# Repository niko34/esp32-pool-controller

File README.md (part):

<h1> ESP32 Pool Controller</h1>

Disclaimer : projet en cours de construction.

Contrôleur automatique de piscine basé sur ESP32 :
- mesure : température, pH, ORP
- pilotage : pompe de filtration, éclairage
- correction avec pompes doseuses : pH et ORP
- interfaces : application web locale, MQTT, API

## 🎯 Fonctionnalités

### Mesures et Contrôle
- **pH** : Mesure via module numérique Atlas Scientific **EZO pH** (I²C). La température de l'eau est transmise au module pour la compensation de température de la mesure.
- **ORP (Redox)** : Mesure via module numérique Atlas Scientific **EZO ORP** (I²C)
- **Température** : Deux sondes Dallas **DS18B20** (eau + circuit/boîtier), identification automatique des rôles sur le bus OneWire
- **Historique** : Historique des mesures
- **Mode d'installation** : Décrit le câblage réel du contrôleur et garantit qu'aucun produit n'est injecté sans circulation d'eau — *PoolController pilote la filtration* (sortie 12 V), *Alimenté par le circuit de filtration*, ou *Filtration externe signalée* (une domotique tierce signale l'état via HTTP/MQTT ; dosage suspendu sans signal récent)
- **Filtration** : Programmation automatique en fonction de la température de l'eau, programmation horaire, manuel
- **Eclairage** : Programmation horaire, manuel
- **Régulation automatique de pH et ORP** : Injection de produit de correction (pH-, chlore liquide) par **régulation proportionnelle temporisée (P)** avec pause de mélange et contrôle de débit PWM. Les mesures sont **lissées** (médiane + EMA) avant d'alimenter la régulation. *(pH+ : option de configuration présente mais non gérée actuellement.)*
- **Consommation de produits** : Estimation de la consommation de produit
- **Application Web locale** : Configuration et visualisation temps réel. Accessible sur le réseau Wifi configuré (`http://poolcontroller.local`) ou un réseau Wifi de en mode point d'accès (`http://192.168.4.1`). Aucune dépendance au Cloud. [Voir les screenshots](screenshots/)
- **API** : Toutes les fonctionnalités sont exposées avec une API
- **MQTT** : Exposition des données sur MQTT. Auto-discovery HomeAssistant.
- **Mise à jour OTA** : Mise à jour firmware via interface web

### Sécurité
- ⚠️ **Limites journalières** : Protection contre le surdosage
- ⚠️ **Limites horaires** : Temps maximum d'injection par heure configurable
- ⚠️ **Watchdog** : Redémarrage automatique en cas de blocage du système (30s)
- ⚠️ **Alertes MQTT** : Notifications en cas d'anomalie

## 📋 Matériel Requis

### Module ESP32 — ⚠️ PSRAM requise

Utiliser un **ESP32-DevKitC-VE** (module **WROVER-E**, ESP32 classique **avec 8 Mo de PSRAM**) — cf. `kicad/esp32-pool-controller/BOM.xlsx`, repère U2.

> ⚠️ **Pourquoi la PSRAM est nécessaire** : la **mise à jour en ligne depuis GitHub**
> (onglet Système → « Vérifier les mises à jour ») ouvre une session TLS qui réclame
> plusieurs blocs de mémoire contigus d'environ 16 Ko. Sur un module **sans PSRAM**
> (WROOM-32), la RAM interne ne les fournit plus de façon fiable une fois le système
> démarré : la vérification échoue de manière intermittente (`BIGNUM - Memory
> allocation failed`). Avec la PSRAM, ces allocations y sont placées automatiquement
> (seuil 4 Ko) et la fonction redevient fiable.
>
> Le firmware **fonctionne** sur un WROOM-32 sans PSRAM (binaire unique, détection
> automatique au démarrage, dégradation gracieuse — depuis la v2.18.0) : régulation,
> interface web, MQTT et **mise à jour manuelle par upload de fichier** restent
> pleinement opérationnels. Seule la vérification/installation automatique depuis
> GitHub est concernée.
>
> Modules déconseillés : l'**ESP32-S3** n'est pas supporté (architecture différente,
> brochage incompatible avec le PCB v2 — les GPIO 22 et 25 utilisés par l'I²C et la
> pompe pH n'y existent pas).

### PCB

Les **sources** KiCad sont versionnées dans [`kicad/`](kicad/) :

- [Schéma électronique](screenshots/Schema.png)
- [PCB](screenshots/PCB.png)
- `kicad/esp32-pool-controller/esp32-pool-controller.kicad_sch` — schéma
- `kicad/esp32-pool-controller/esp32-pool-controller.kicad_pcb` — routage
- `kicad/esp32-pool-controller/BOM.xlsx` — nomenclature (source ; le `BOM.csv`
  s'en déduit avec `python3 tools/bom_export.py`)

Les **fichiers de fabrication** (gerbers, perçage) ne sont pas versionnés : ils se
régénèrent avec `./scripts/build-gerbers.sh` et sont publiés comme assets des
releases `pcb-vX`. Voir « Fichiers générés et releases » dans `CLAUDE.md`.

### Boîtier

Les sources FreeCAD et les STL d'impression 3D sont conservés **hors du dépôt**.

## 🧭 Reprendre le projet

Cette section s'adresse à quiconque récupère le dépôt — y compris son auteur dans
deux ans. Elle dit **où est quoi** et **comment on travaille ici**.

### Outils nécessaires

| Outil | Pour quoi | Indispensable ? |
|---|---|---|
| **PlatformIO** | compiler, téléverser, lancer les tests | oui |
| **Node.js** | `minify.js`, appelé par `build_fs.sh` | oui |
| **Chrome / Chromium** | générer les PDF de documentation | pour les releases |
| **`gh`** (GitHub CLI) | publier les releases | pour les releases |
| **KiCad 7+** | ouvrir le PCB, générer les gerbers | pour le matériel |
| **Python 3** | `tools/*.py` (BOM, coredump, couverture) | ponctuel |

⚠️ Sur macOS, `kicad-cli` et Chrome ne sont pas dans le `PATH` : les scripts
`scripts/*.sh` sondent aussi les emplacements `.app`.

### Repartir d'un clone (conteneur, autre machine)

```bash
# Debian / Ubuntu
sudo apt install -y python3 python3-pip nodejs npm chromium imagemagick zip gh
pip install --user platformio
# facultatif, seulement pour le PCB :
sudo apt install -y kicad

git clone https://github.com/niko34/esp32-pool-controller.git
cd esp32-pool-controller
pio pkg install -e esp32dev_core3   # télécharge la plateforme et les libs
pio test -e native                  # doit être vert
pio run                             # doit compiler
```

**Ce qui fonctionne depuis un clone nu** : les agents, les skills et les
commandes, les specs, les tests natifs, la compilation, la génération des PDF et
celle des gerbers. **Trois workflows GitHub Actions rejouent les trois premiers à
chaque push et à chaque PR** — tests natifs + couverture, compilation
`pio run -e esp32dev_core3`, et hygiène des specs (`./tools/check_specs.sh`,
lançable en local) : ce n'est pas une promesse, c'est une preuve. Voir
[docs/BUILD.md](docs/BUILD.md#intégration-continue-github-actions). Les scripts détectent leurs outils et échouent avec un message explicite
si l'un manque.

**Ce qui ne fonctionne pas à distance** : le déploiement sur l'appareil. Son mot
de passe n'est pas dans le dépôt — délibérément — et il vit sur un réseau local.
Il faut être sur le même réseau, et fournir le mot de passe :

```bash
./ota_update.sh firmware <adresse-ip> <mot-de-passe>
```

**Confort dégradé** : `.claude/settings.local.json` n'est pas versionné (il
contient des chemins absolus propres à une machine). Le `settings.json` partagé
couvre l'essentiel — y compris les garde-fous `deny` et `ask` — mais vous
confirmerez plus de commandes qu'en local. C'est le prix d'une configuration
qui ne présume rien de la machine.

### Où est quoi

```
src/            firmware C++ (ESP32, Arduino)      data/     interface web (vanilla JS)
test/           tests natifs — logique pure         docs/     doc technique, ADR, guides
specs/          LA SOURCE DE VÉRITÉ des demandes    kicad/    sources du PCB
scripts/        livrables de release (PDF, gerbers) tools/    utilitaires de développement
.claude/        agents, skills et commandes         builds/   archive LOCALE des binaires
```

### Comment on travaille

Le cycle est décrit en détail dans **[CLAUDE.md](CLAUDE.md)**. En résumé :

1. **Une demande = une spec** dans `specs/features/todo/`, au format du template.
   Elle se déplace vers `doing/` quand le travail commence, `done/` quand il finit,
   enrichie des notes techniques et des décisions prises.
2. **Le travail passe par des agents spécialisés** (`.claude/agents/`) :
   conception, implémentation firmware ou web, tests, revue, documentation.
   ⚠️ **`pool-chemistry` est obligatoire** dès qu'on touche au dosage, à la
   régulation ou à la calibration des sondes — ce sont les pompes qui injectent de
   l'acide et du chlore dans un bassin.
3. **Les tests natifs sont non négociables** : `pio test -e native` doit rester
   vert, et tout test neuf est **validé par mutation** — on casse volontairement le
   code qu'il protège pour vérifier qu'il meurt. Plusieurs défauts réels de ce
   projet n'ont été trouvés que comme ça.
4. **Toute décision structurante devient un ADR** dans `docs/adr/`. Les ADR sont
   immuables : on les amende d'une bannière, on ne réécrit pas leur histoire.

### Les commandes utiles

```bash
pio run                    # compiler (env unique esp32dev_core3)
pio test -e native         # 33 suites, ~1 286 cas
./build_fs.sh              # construire le filesystem web
./deploy.sh all            # flasher par USB (firmware + filesystem)
./deploy.sh ota-firmware   # mettre à jour par WiFi
./tools/coverage.sh        # couverture des tests
/release                   # publier une version firmware + doc
/release-pcb               # publier des fichiers de fabrication PCB
```

Il n'y a **qu'un seul environnement matériel**, `esp32dev_core3`. L'ancien repli
core Arduino 2.x a été retiré en v2.42.1 : il n'était plus compilable, plus
flashable, et aucun binaire de secours n'avait jamais été archivé
([ADR-0069](docs/adr/0069-retrait-repli-core-2.md)).

### Ce qui n'est pas dans le dépôt, et pourquoi

Les **fichiers générés** n'y sont pas : PDF de documentation, gerbers de
fabrication, firmware compilé. Ils sont attachés aux **releases GitHub**, où ils
sont horodatés et associés à un tag. Voir « Fichiers générés et releases » dans
[CLAUDE.md](CLAUDE.md).

**Deux exceptions volontaires**, parce que ces fichiers ne sont pas *générés* mais
*relevés* — rien ne les régénère :

- **`docs/incidents/`** — les coredumps de production et leurs traces décodées. Un
  coredump n'existe qu'une fois : il est écrasé au crash suivant.
- **L'ELF est attaché à chaque release** (~29 Mo) en plus du `.bin`. `esp-coredump`
  vérifie le SHA256 de l'image et refuse un ELF qui ne correspond pas : sans celui
  de la version exacte, un crash reste indéchiffrable.

`builds/` contient l'archive **locale** des ELF de tous les builds (2,6 Go) et
n'est pas versionné.

Les **sources FreeCAD** du boîtier et les exports STL sont conservés hors dépôt.

## 🚀 Installation

### PlatformIO (Recommandé)

1. **Cloner le projet**
   ```bash
   git clone https://github.com/niko34/esp32-pool-controller.git
   cd esp32-pool-controller
   ```

2. **Ouvrir avec VS Code + PlatformIO**
   ```bash
   code .
   ```

3. **Compiler et déployer**

   L'unique environnement de build est **`esp32dev_core3`** (core Arduino 3.x / ESP-IDF 5 via pioarduino) — bootloader **et** application, depuis la v2.20.4 ([ADR-0042](docs/adr/0042-core3-environnement-par-defaut.md)). L'environnement de repli core 2 a été retiré en v2.42.1 ([ADR-0069](docs/adr/0069-retrait-repli-core-2.md)) :

   ```bash
   pio run                              # core 3, env unique
   ./deploy.sh all                      # firmware + filesystem
   ```

   ℹ️ Premier build sur une machine neuve : `pio pkg install -e esp32dev_core3` (téléchargement du framework). Voir [BUILD.md](docs/BUILD.md#lenvironnement-firmware-unique).

   **Via USB** (obligatoire pour la première installation, et pour tout changement de bootloader ou de table de partitions) :
   ```bash
   ./deploy.sh all       # Compile et upload firmware + filesystem
   ./deploy.sh firmware  # Firmware uniquement
   ./deploy.sh fs        # Filesystem uniquement
   ```

   **Via WiFi OTA** (mises à jour suivantes, une fois la première installation USB effectuée) :
   ```bash
   ./deploy.sh ota-all       # Compile et envoie firmware + filesystem
   ./deploy.sh ota-firmware  # Firmware uniquement
   ./deploy.sh ota-fs        # Filesystem uniquement
   ```

   Voir [UPDATE_GUIDE.md](docs/UPDATE_GUIDE.md) pour plus de détails sur les méthodes de mise à jour.

4. **Moniteur série**
   ```bash
   pio device monitor -b 115200
   ```

### Première connexion et accès à l'interface Web

1. **Première connexion**
   - Au démarrage, l'ESP32 crée un point d'accès WiFi `PoolControllerAP`
   - Le mot de passe WiFi AP est **unique par appareil**, généré aléatoirement au premier boot et stocké en NVS
   - Il s'affiche en clair dans le moniteur série **tant que le wizard de configuration n'est pas complété** :
     ```
     [INFO] AP démarré: PoolControllerAP
     [INFO] AP Password: XXXXXXXX
     [INFO] IP AP: 192.168.4.1
     ```
   - Le flash USB (`./deploy.sh all`) **enchaîne le moniteur série** : l'ouverture du port redémarre l'ESP32, le boot est donc capté depuis sa première ligne, sans manœuvre particulière
   - Coller le mot de passe sur une étiquette sur le boîtier
   - Se connecter au réseau `PoolControllerAP` avec ce mot de passe et accéder à l'assistant de configuration http://192.168.4.1

   > **Après le wizard complété**, si l'AP redémarre (ex : perte WiFi), le mot de passe n'est plus affiché en clair dans les logs pour des raisons de sécurité. Utiliser l'étiquette ou l'API :
   > ```
   > GET http://poolcontroller.local/auth/ap-password
   > ```

   > **Forcer la génération d'un nouveau mot de passe AP** (ex : fabrication d'un nouvel appareil, remplacement d'étiquette) : utiliser l'option `factory`, qui efface la flash, réinstalle, ré-efface la NVS **en dernier**, puis **ouvre le moniteur série automatiquement**. Le mot de passe s'affiche dans les premières lignes de boot — inutile d'ouvrir un moniteur à la main, et inutile de le lancer *avant* d'alimenter l'appareil.
   > ```bash
   > ./deploy.sh factory
   > ```
   > ```
   > === MOT DE PASSE AP WIFI: XXXXXXXX ===
   > ```
   > ⚠️ Efface **toute** la flash (firmware, filesystem, NVS, historique). À n'utiliser que sur un appareil qu'on réinitialise complètement. Voir [UPDATE_GUIDE.md](docs/UPDATE_GUIDE.md#récupérer-le-mot-de-passe-wifi-ap).

2. **Accès interface web**
   - `http://poolcontroller.local` si réseau wifi configuré, sinon se connecter au réseau AP PoolControllerAP et utiliser l'adresse http://192.168.4.1
   - Onglets disponibles:
     - **Tableau de bord** : Visualisation temps réel pH/ORP/Température
     - **Filtration** : Contrôle et programmation de la pompe de filtration
     - **Éclairage** : Contrôle et programmation de l'éclairage
     - **Température** : Historique et calibration de la sonde de température
     - **pH** : Mesure, historique, calibration et réglages dosage pH
     - **ORP** : Mesure, historique, calibration et réglages dosage chlore
     - **Produits** : Suivi de la consommation des produits chimiques
     - **Paramètres** : WiFi, MQTT, heure, sécurité, régulation, système

### Calibration Capteurs

#### Calibration pH (Atlas Scientific EZO pH)

La calibration est gérée **en interne par le module EZO** (commandes I²C `Cal,...`), mémorisée dans le module lui-même — il n'y a ni offset/pente stockés côté ESP32, ni EEPROM, ni librairie analogique. Elle se déclenche depuis l'interface web, onglet **pH** → carte **Calibration** (deux sous-blocs indépendants). Le module EZO pH accepte les points **milieu (pH 7.0)**, **bas (pH 4.0)** et, optionnellement, **haut**. La régulation automatique du pH est **inhibée tant que les 2 points (mid + low) ne sont pas calibrés**.

**Calibration via l'interface web** :
1. Aller dans l'onglet **pH** → carte **Calibration**
2. Rincer la sonde à l'eau distillée, la plonger dans la solution tampon **pH 7.00**, attendre stabilisation (~1 min)
3. Cliquer sur **« Calibrer le point 7.0 »** (sous-bloc *Point milieu*)
4. Rincer la sonde, la plonger dans la solution **pH 4.00**, attendre stabilisation
5. Cliquer sur **« Calibrer le point 4.0 »** (sous-bloc *Point bas*)

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
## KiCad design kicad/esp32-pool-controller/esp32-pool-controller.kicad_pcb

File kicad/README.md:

# Matériel — point d'entrée

Sources KiCad du PCB du contrôleur de piscine.

⚠️ **Les sources de ce dossier sont GELÉES sauf demande explicite** (règle 5 de
[`CLAUDE.md`](../CLAUDE.md)) : on ne modifie ni le schéma ni le routage au fil
d'une tâche logicielle.

## Fichiers

| Fichier | Rôle |
|---|---|
| `esp32-pool-controller.kicad_sch` · `.kicad_pcb` · `.kicad_pro` | Sources, **versionnées** |
| `SymLib.kicad_sym` · `sym-lib-table` | Bibliothèque de symboles du projet |
| `BOM.xlsx` | **Nomenclature de référence** — ⛔ toute correction se fait ICI |

⛔ **`BOM.csv` est un DÉRIVÉ**, généré par `python3 tools/bom_export.py` depuis le
`.xlsx`, donc ignoré par git. ⚠️ **Ne jamais le corriger à la main** : la prochaine
exécution du script l'écrase.

Les fichiers de fabrication (gerbers, perçage, zips) ne sont **pas** versionnés :
ils se régénèrent avec `./scripts/build-gerbers.sh` et deviennent les assets d'une
release `pcb-vX` via `/release-pcb`.

---

## 🔴 Deux défauts MATÉRIELS non résolus — à instruire avant toute révision du PCB

**Ils ont été sortis du backlog logiciel le 2026-10-17**, sur décision de
l'utilisateur : *« ces investigations sont du ressort de l'humain qui conçoit le
PCB »*. ⛔ **Clôturées ne veut pas dire résolues** — elles attendent une personne
avec des instruments, pas une session de travail.

### 1. Perturbation de mode commun sur les électrodes pH/ORP
[`specs/features/done/feature-137-perturbation-de-mode-commun-sur-les-electrodes.md`](../specs/features/done/feature-137-perturbation-de-mode-commun-sur-les-electrodes.md)

Le pH brut est **anti-corrélé et presque à deux niveaux**, et **la voie ORP voit la
même perturbation** : les deux électrodes subissent un **mode commun**. Mécanisme
suspecté : couplage électrique via le verre (~100 MΩ) avec les **courants de fuite
de la pompe de filtration** — mesure nettement meilleure sur batterie.

⚠️ **Ce que ça coûte aujourd'hui** : le 2026-10-16, l'eau réelle était à **pH 8**
et la sonde lisait **6,9**. Une correction de **+1,00** a dû être posée — **le
double de l'ancienne borne**, retirée pour la rendre possible (ADR-0114, v2.82.0).
⛔ **Le logiciel ne corrige pas ce défaut, il le COMPENSE** — sur la grandeur même
qui décide des injections d'acide.

⇒ C'est la **seule voie** qui assainirait le signal **à la source**.

### 2. Transitoire de reprise de filtration
[`specs/features/done/feature-069-investigation-materielle-sonde-ph.md`](../specs/features/done/feature-069-investigation-materielle-sonde-ph.md)

Trois matins consécutifs (02-04/09/2026), même signature : brut **normal** à la
remise en circulation, plongeon à **5,60-5,71** quelques minutes après, retour à la
normale en **30 à 48 min**, ⚠️ **l'ORP plongeant en parallèle** (−56 à −74 mV).

⛔ **Les cinq hypothèses restent ouvertes** (chambre désamorcée · bulles piégées ·
effet électrique au démarrage · eau réellement acide · sonde vieillissante).

⭐ **Le relevé qui tranche** : **deux bandelettes simultanées**, une au **bassin** et
une au **refoulement**, à **t+2** et **t+15 min** après la reprise. C'est le seul
qui sépare « l'eau est réellement acide » de « la sonde lit faux ». ⚠️ Tout le reste
en découle.
⛔ **Préalable de sécurité** : régulation pH en **manuel** pendant toute
manipulation de sonde.

### Lié, et toujours ouvert côté logiciel
[`bug-135`](../specs/features/todo/bug-135-butee-brute-ph-se-declenche-sur-une-lecture-isolee.md)
— la butée de sécurité brute se déclenche sur ces lectures isolées. ⚠️ **Même
cause** : tant que le mode commun est là, le logiciel doit composer avec un signal
qui alterne entre deux niveaux.

## Références
- [ADR-0012 — mapping GPIO du PCB v2](../docs/adr/0012-mapping-gpio-pcb-v2.md)
- [ADR-0097 — Le filtre lisse, le dosage juge](../docs/adr/0097-le-filtre-lisse-le-dosage-juge.md) — ce que le logiciel fait du bruit, faute de pouvoir le supprimer
- [feature-097 — Seuil de stabilité sur données terrain](../specs/features/done/feature-097-seuil-de-stabilite-sur-donnees-terrain.md) — la campagne qui **caractérise** le bruit (⛔ sans l'expliquer)

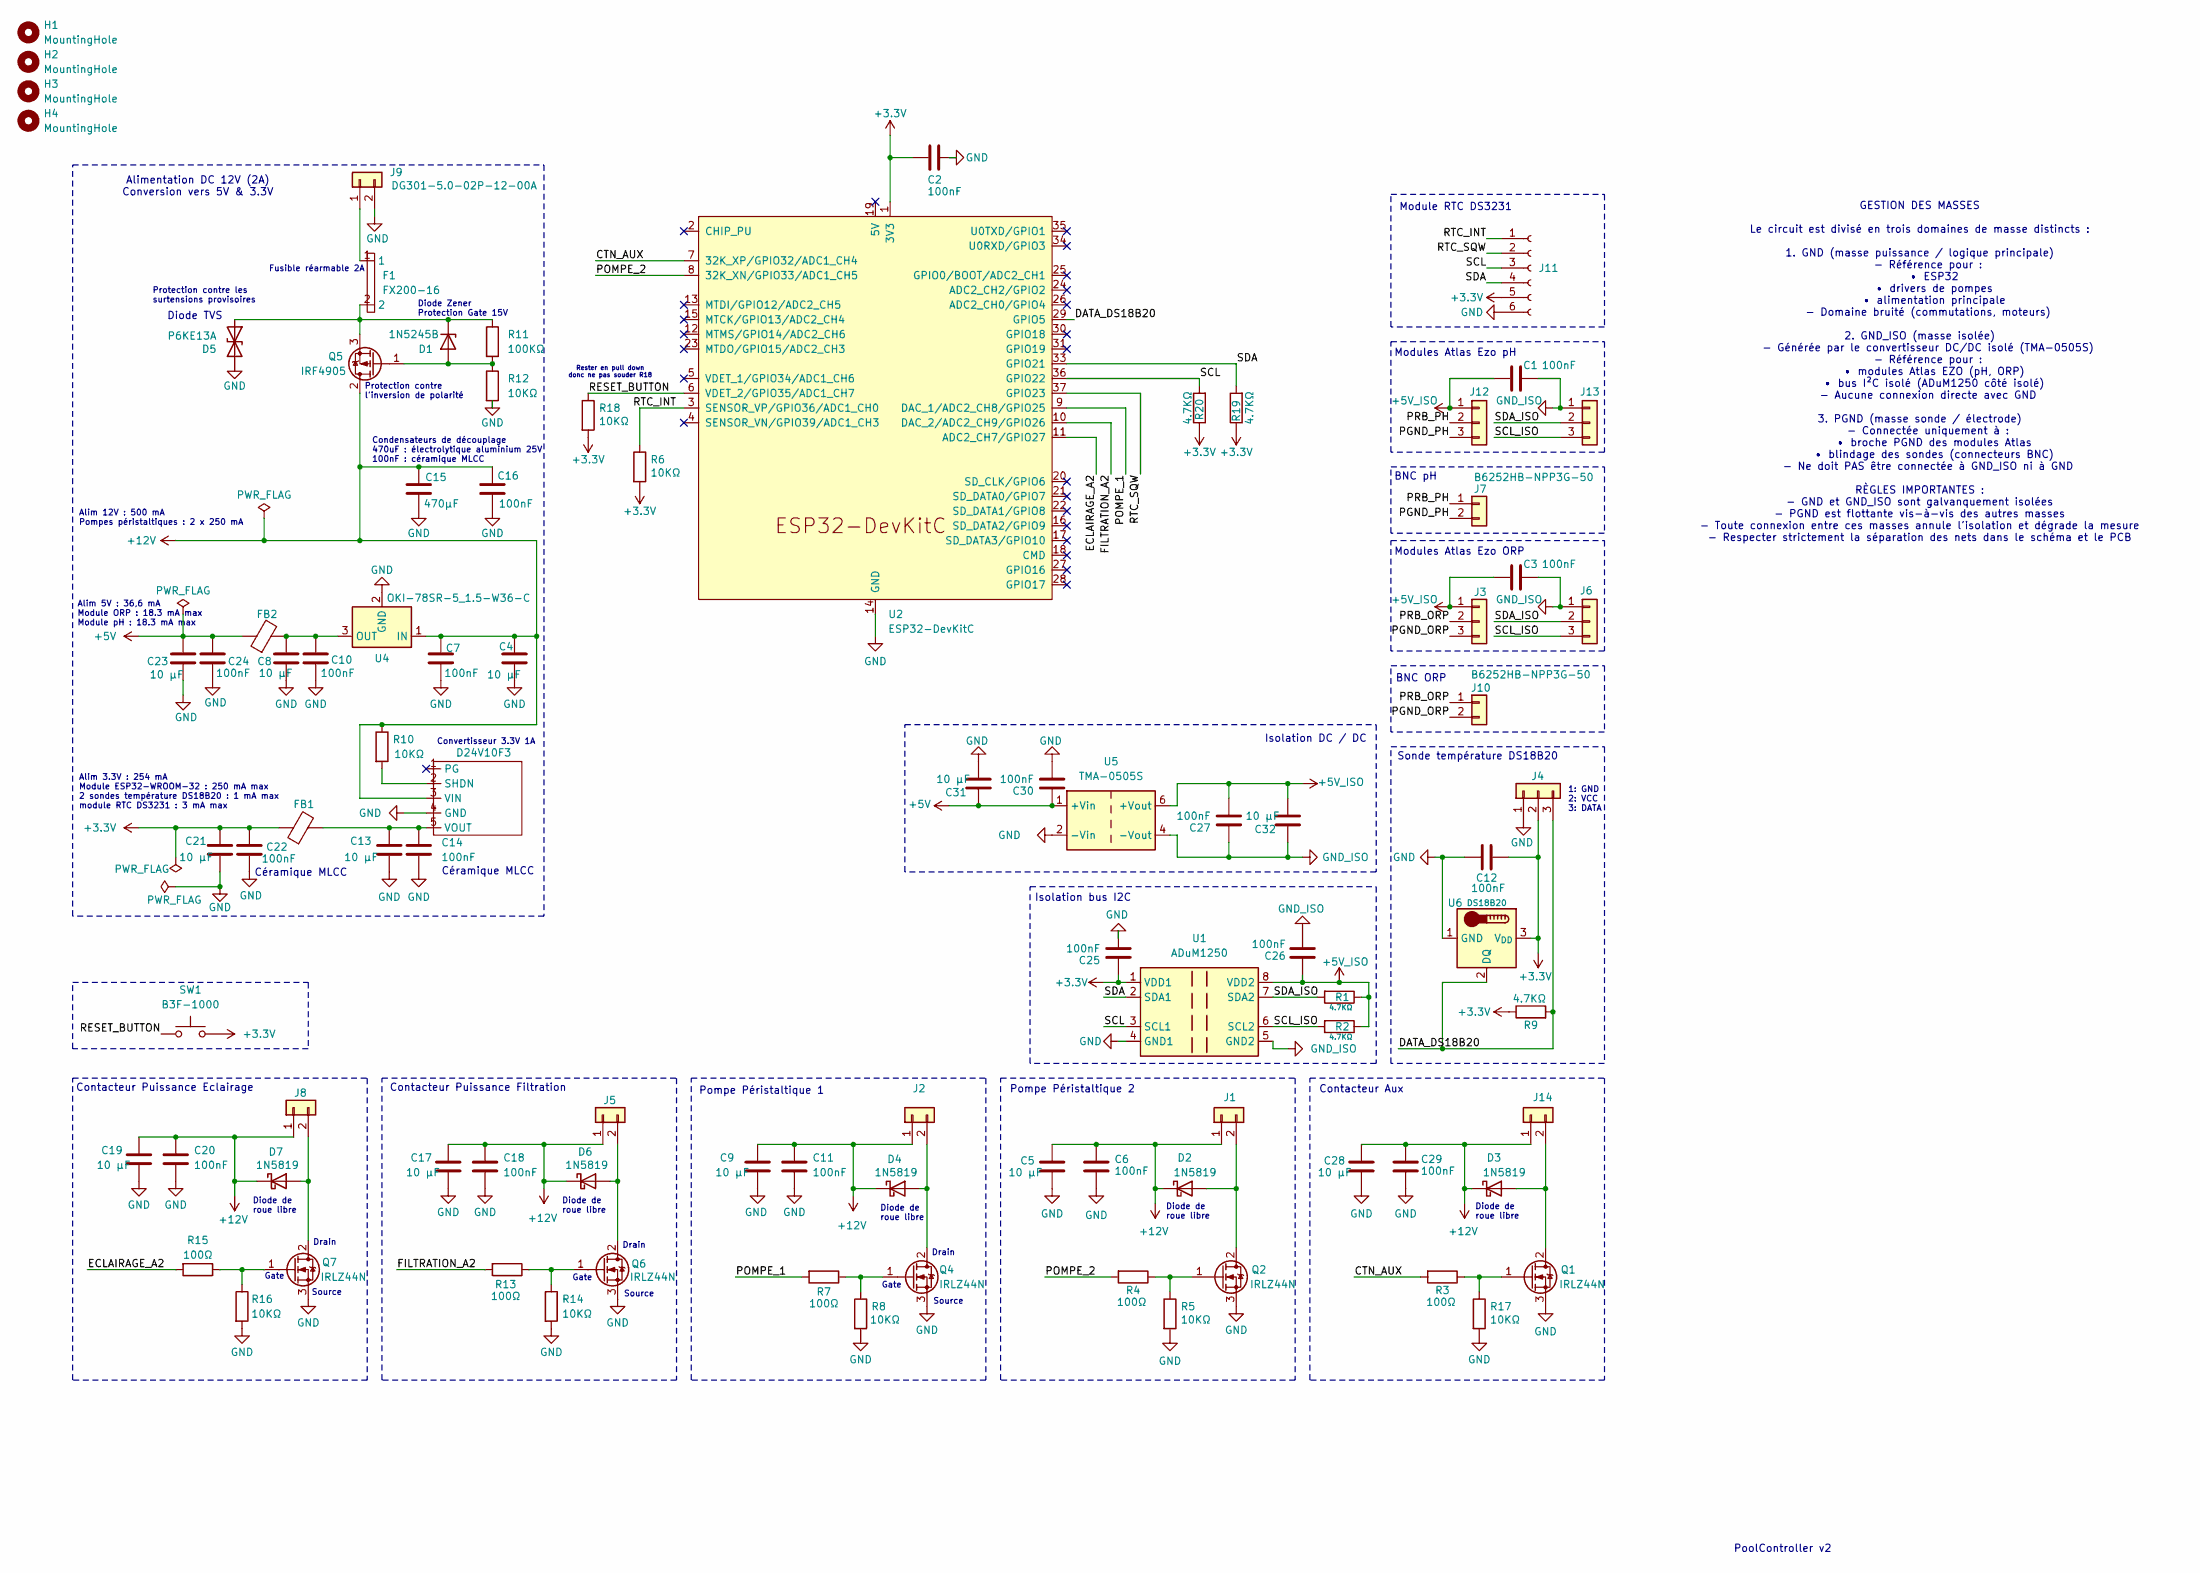
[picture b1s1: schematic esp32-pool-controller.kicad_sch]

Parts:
C1, C2, C3, C6, C7, C10, C11, C12, C14, C16, C18, C20, C22, C24, C25, C26, C27, C29, C30: 100nF; C_Disc_D3.8mm_W2.6mm_P2.50mm
C4, C5, C8, C9, C13, C17, C19, C21, C23, C28, C31, C32: 10 µF; C_Disc_D6.0mm_W4.4mm_P5.00mm
C15: 470µF; CP_Radial_D10.0mm_P5.00mm
D1: 1N5245B; D_DO-35_SOD27_P7.62mm_Horizontal
D2, D3, D4, D6, D7: 1N5819; D_DO-15_P10.16mm_Horizontal
D5: P6KE13A; D_DO-15_P10.16mm_Horizontal
F1: FX200-16; Fuse_Bourns_MF-RHT200
FB1, FB2: BBPY00321611601Y00; R_1206_3216Metric
H1, H2, H3, H4: MountingHole; MountingHole_3.2mm_M3
J1, J2, J5, J8, J9, J14: DG301-5.0-02P-12-00A; Altech_AK100_1x02_P5.00mm
J3, J6, J12, J13: Conn_01x03; PinSocket_1x03_P2.54mm_Vertical
J4: DG301-5.0-03P-12-00AH; JST_XH_B3B-XH-A_1x03_P2.50mm_Vertical
J7, J10: B6252HB-NPP3G-50; BNC_Amphenol_B6252HB-NPP3G-50_Horizontal
J11: Conn_01x06_Socket; PinSocket_1x06_P2.54mm_Vertical
Q1, Q2, Q4, Q6, Q7: IRLZ44N; TO-220-3_Vertical
Q5: IRF4905; TO-220-3_Vertical
R1, R2, R9, R19, R20: 4.7KΩ; R_Axial_DIN0207_L6.3mm_D2.5mm_P10.16mm_Horizontal
R3, R4, R7, R13, R15: 100Ω; R_Axial_DIN0207_L6.3mm_D2.5mm_P10.16mm_Horizontal
R5, R6, R8, R10, R12, R14, R16, R17, R18: 10KΩ; R_Axial_DIN0207_L6.3mm_D2.5mm_P10.16mm_Horizontal
R11: 100KΩ; R_Axial_DIN0207_L6.3mm_D2.5mm_P10.16mm_Horizontal
SW1: B3F-1000; SW_PUSH_6mm
U1: ADuM1250; DIP-8_W7.62mm
U2: ESP32-DevKitC
U3: D24V10F3; Pololu_D24V10F3
U4: OKI-78SR-5_1.5-W36-C; Converter_DCDC_Murata_OKI-78SR_Vertical
U5: TMA-0505S; Converter_DCDC_TRACO_TMA-05xxS_12xxS_Single_THT
U6: DS18B20; TO-92_Inline

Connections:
+3.3V: C2.2, C12.2, C21.1, C22.1, C25.1, FB1.1, J4.2, J11.5, R6.2, R9.1, R18.2, R19.1, R20.1, SW1.2, U1.1 (VDD1), U2.1 (3V3), U6.3 (V_{DD})
+5V: C23.1, C24.1, C30.1, C31.2, FB2.1, U5.1 (+Vin)
+5V_ISO: C1.1, C3.1, C26.1, C27.2, C32.1, J3.1, J12.1, R1.1, R2.1, U1.8 (VDD2), U5.6 (+Vout)
+12V: C4.1, C5.1, C6.1, C7.1, C9.1, C11.1, C15.1, C16.1, C17.1, C18.1, C19.1, C20.1, C28.1, C29.1, D2.1 (K), D3.1 (K), D4.1 (K), D6.1 (K), D7.1 (K), J1.1, J2.1, J5.1, J8.1, J14.1, Q5.2 (D), R10.1, U3.3 (VIN), U4.1 (IN)
/CTN_AUX: R3.2, U2.7 (32K_XP/GPIO32/ADC1_CH4)
/DATA_DS18B20: J4.3, R9.2, U2.29 (GPIO5), U6.2 (DQ)
/ECLAIRAGE_A2: R15.2, U2.11 (ADC2_CH7/GPIO27)
/FILTRATION_A2: R13.2, U2.10 (DAC_2/ADC2_CH9/GPIO26)
/PGND_ORP: J3.3, J10.2
/PGND_PH: J7.2, J12.3
/POMPE_1: R7.2, U2.9 (DAC_1/ADC2_CH8/GPIO25)
/POMPE_2: R4.2, U2.8 (32K_XN/GPIO33/ADC1_CH5)
/PRB_ORP: J3.2, J10.1
/PRB_PH: J7.1, J12.2
/RESET_BUTTON: R18.1, SW1.1, U2.6 (VDET_2/GPIO35/ADC1_CH7)
/RTC_INT: J11.1, R6.1, U2.3 (SENSOR_VP/GPIO36/ADC1_CH0)
/RTC_SQW: J11.2, U2.37 (GPIO23)
/SCL: J11.3, R20.2, U1.3 (SCL1), U2.36 (GPIO22)
/SCL_ISO: J6.3, J13.3, R2.2, U1.6 (SCL2)
/SDA: J11.4, R19.2, U1.2 (SDA1), U2.33 (GPIO21)
/SDA_ISO: J6.2, J13.2, R1.2, U1.7 (SDA2)
GND: C2.1, C4.2, C5.2, C6.2, C7.2, C8.2, C9.2, C10.2, C11.2, C12.1, C13.2, C14.2, C15.2, C16.2, C17.2, C18.2, C19.2, C20.2, C21.2, C22.2, C23.2, C24.2, C25.2, C28.2, C29.2, C30.2, C31.1, D5.2 (A2), J4.1, J9.2, J11.6, Q1.3 (S), Q2.3 (S), Q4.3 (S), Q6.3 (S), Q7.3 (S), R5.2, R8.2, R12.2, R14.2, R16.2, R17.2, U1.4 (GND1), U2.14 (GND), U2.32 (GND), U2.38 (GND), U3.4 (GND), U4.2 (GND), U5.2 (-Vin), U6.1 (GND)
GND_ISO: C1.2, C3.2, C26.2, C27.1, C32.2, J6.1, J13.1, U1.5 (GND2), U5.4 (-Vout)
unnamed: D1.2 (A), Q5.1 (G), R11.2, R12.1
unnamed: D1.1 (K), D5.1 (A1), F1.2, Q5.3 (S), R11.1
unnamed: D2.2 (A), J1.2, Q2.2 (D)
unnamed: D3.2 (A), J14.2, Q1.2 (D)
unnamed: D4.2 (A), J2.2, Q4.2 (D)
unnamed: D6.2 (A), J5.2, Q6.2 (D)
unnamed: D7.2 (A), J8.2, Q7.2 (D)
unnamed: F1.1, J9.1
unnamed: Q1.1 (G), R3.1, R17.1
unnamed: Q2.1 (G), R4.1, R5.1
unnamed: Q4.1 (G), R7.1, R8.1
unnamed: Q6.1 (G), R13.1, R14.1
unnamed: Q7.1 (G), R15.1, R16.1
unnamed: R10.2, U3.2 (SHDN)
unnamed: C13.1, C14.1, FB1.2, U3.5 (VOUT)
unnamed: C8.1, C10.1, FB2.2, U4.3 (OUT)

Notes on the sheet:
Contacteur Aux
Alimentation DC 12V (2A) Conversion vers 5V & 3.3V
Protection contre l'inversion de polarité
Contacteur Puissance Eclairage
Pompe Péristaltique 2
Module RTC DS3231
Céramique MLCC
Diode de roue libre
PoolController v2
Gate
Modules Atlas Ezo ORP
Contacteur Puissance Filtration
Drain
Rester en pull down donc ne pas souder R18
Sonde température DS18B20
Diode Zener Protection Gate 15V
Alim 3.3V : 254 mA Module ESP32-WROOM-32 : 250 mA max 2 sondes température DS18B20 : 1 mA max module RTC DS3231 : 3 mA max
GESTION DES MASSES Le circuit est divisé en trois domaines de masse distincts : 1. GND (masse puissance / logique principale) - Référence pour : • ESP32 • drivers de pompes • alimentation principale - Domaine bruité (commutations, moteurs) 2. GND_ISO (masse isolée) - Générée par le convertisseur DC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
Source
1: GND 2: VCC 3: DATA
Alim 12V : 500 mA Pompes péristaltiques : 2 x 250 mA
Diode TVS
Alim 5V : 36,6 mA Module ORP : 18.3 mA max Module pH : 18.3 mA max
Isolation bus I2C
Modules Atlas Ezo pH
Convertisseur 3.3V 1A
Pompe Péristaltique 1
Isolation DC / DC
Fusible réarmable 2A
Condensateurs de découplage 470uF : électrolytique aluminium 25V 100nF : céramique MLCC
BNC ORP
BNC pH
Protection contre les surtensions provisoires

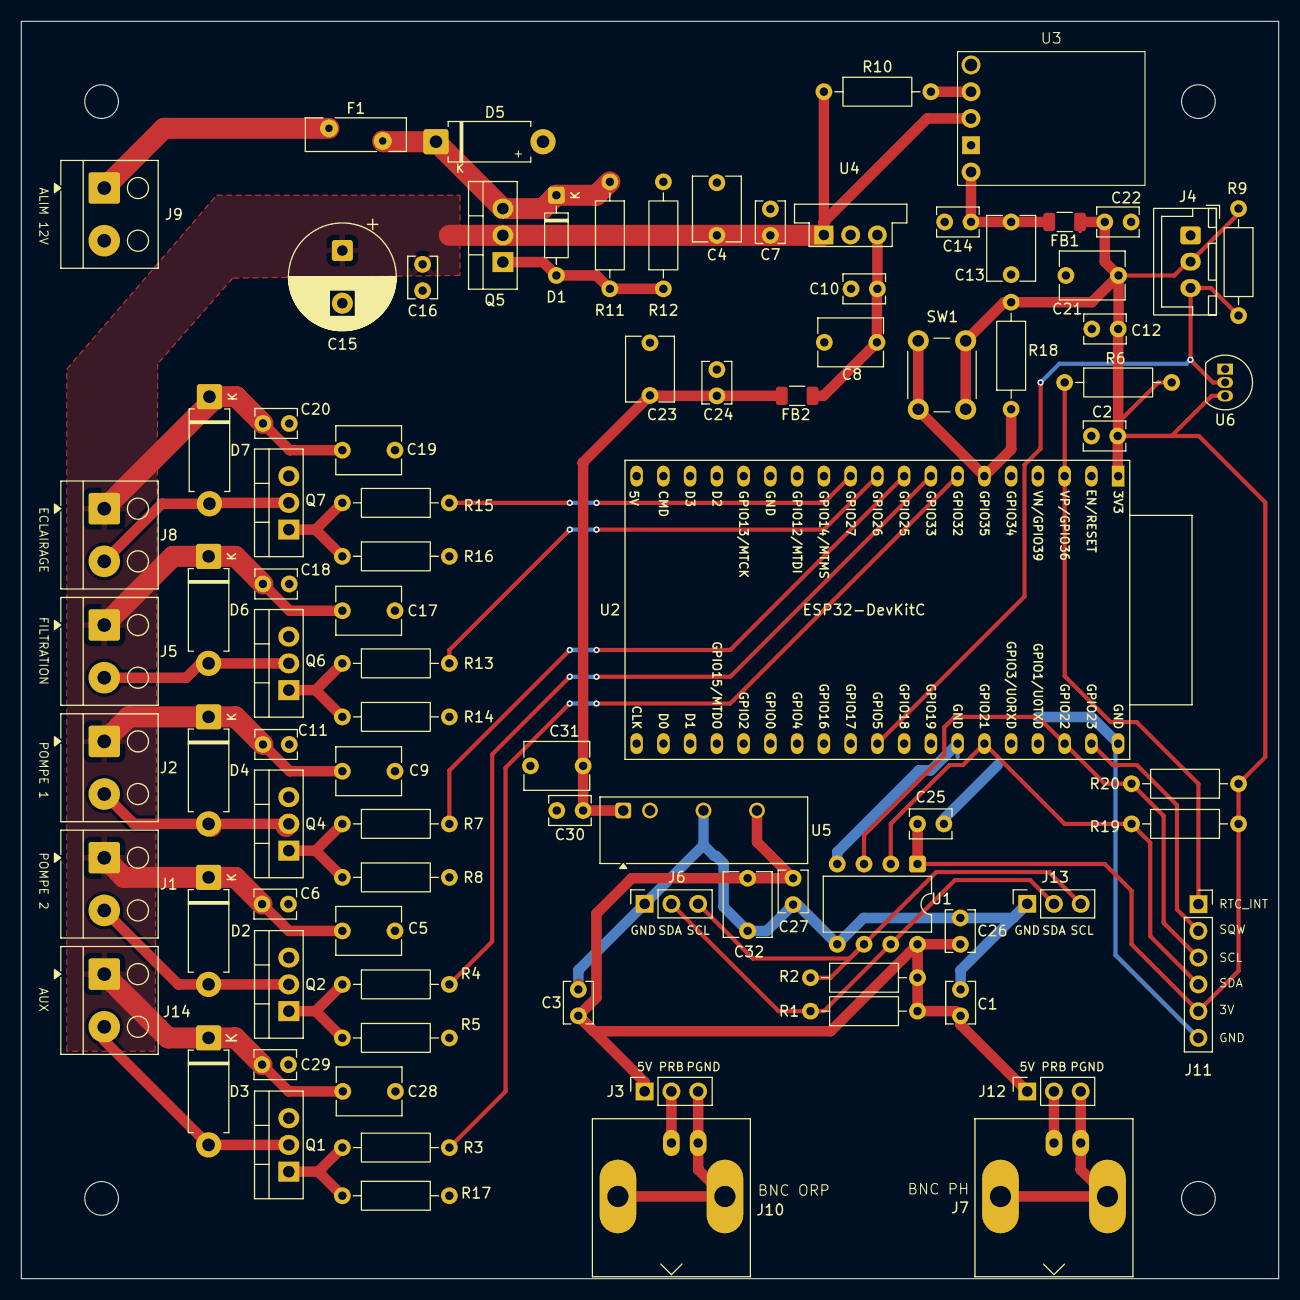
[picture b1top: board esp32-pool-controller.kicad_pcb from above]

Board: 2 copper layers, 119.4 x 119.4 mm, 93 parts (0 on the bottom side), 39 nets.

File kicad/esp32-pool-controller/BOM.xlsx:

Reference | Qty | Value | Comment | Link
C1,C2,C3,C6,C7,C10,C11,C12,C14,C16,C18,C20,C22,C24,C25,C26,C27,C29,C30 | 19 | K104K10X7RF5UL2 | 100nF céramique X7R 10% 2.54mm | https://www.tme.eu/fr/details/k104k10x7rf5ul2/condensateurs-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
C4,C5,C8,C9,C13,C17,C19,C21,C23,C28,C31,C32 | 12 | FG20X7R1H106KRT06 | 10µF céramique mlcc X7R 10% 5.1mm | https://www.tme.eu/fr/details/fg20x7r1h106krt06/condensateur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
C15 | 1 | ECA1EHG471B | 470µF Electrolytique 25V | https://www.tme.eu/fr/details/eca1ehg471b/condensateurs-elec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
D1 | 1 | 1N5245B | Diode: Zener; 0,5W; 15V | https://www.tme.eu/fr/details/1n5245btr/diodes-zener-tht/onsemi/
D2,D3,D4,D6,D7 | 5 | 1N5819 | Diode: redressement Schottky; THT; 40V; 1A; DO15; Ufmax: 900mV | https://www.tme.eu/fr/details/1n5819-dio/diodes-schottky-tht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
D5 | 1 | P6KE13A |  | https://www.tme.eu/fr/details/p6ke13a-dio/diodes-unidirectio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
F1 | 1 | 30R185UU | Fusible PPTC 30VDC courant maintien 1.85A THT 5.1mm | https://fr.farnell.com/littelfuse/30r185uu/polyfuse-ptc-radi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
FB1,FB2 | 2 | BBPY00321611601Y00 |  | https://www.tme.eu/fr/details/bbpy00321611601y00/ferrites-pe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
J1,J2,J5,J8,J9,J14 | 6 | DG301-5.0-02P-12-00A |  | https://www.tme.eu/fr/details/dg301-5.0-2p12/blocs-de-bornes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
J3,J6,J11,J12,J13 | 5 | DS1002-03-1*20131 | Pour connecteur ESP32, module RTC, module pH, module ORPÉ | https://www.tme.eu/fr/details/zl307-1x20/batis-de-prises-et-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
J4 | 1 | DG301-5.0-03P-12-00AH | Connecteur JST 3P
J7,J10 | 2 | B6252HB-NPP3G-50 |  | https://www.tme.eu/fr/details/b6252hb-npp3g-50/connecteurs-b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
Q1,Q2,Q4,Q6,Q7 | 5 | IRLZ44NPBF | Transistor: N-MOSFET; unipolaire; 55V; 41A; 83W; TO220AB | https://www.tme.eu/fr/details/irlz44npbf/transistors-tht-a-c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
Q5 | 1 | IRF4905PBF | Transistor: P-MOSFET; unipolaire; -55V; -74A; 200W; TO220AB | https://www.tme.eu/fr/details/irf4905pbf/transistors-a-canal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
R1,R2,R9,R19,R20 | 5 | 4.7KΩ | Idéalement metal film 1% 0,25W. Si 1% pas disponible, 5% possible.
R3,R4,R7,R13,R15 | 5 | 100Ω | Idéalement metal film 1% 0,25W. Si 1% pas disponible, 5% possible.
R5,R6,R8,R10,R12,R14,R16,R17,R18 | 9 | 10KΩ | Idéalement metal film 1% 0,25W. Si 1% pas disponible, 5% possible.
R11 | 1 | 100KΩ | Idéalement metal film 1% 0,25W. Si 1% pas disponible, 5% possible.
SW1 | 1 | B3F-1000 |  | https://www.tme.eu/fr/details/b3f-1000/micro-interrupteurs-t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
U1 | 1 | ADuM1250 |  | https://www.tme.eu/fr/details/adum1250arz/circuits-integres-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
 | 1 | Adaptateur SOP8 vers DIP8 |  | https://www.gotronic.fr/art-adaptateur-so8-dil8-19701.htm?sr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
U2 | 1 | ESP32-DevKitC-VE | Avec de la PSRAM | https://fr.aliexpress.com/item/1005004686938288.html?spm=a2g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
U3 | 1 | D24V10F3 |  | https://www.tme.eu/fr/details/pololu-2830/onduleurs/pololu/3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
U4 | 1 | OKI-78SR-5_1.5-W36-C
U5 | 1 | TMA-0505S |  | https://www.tme.eu/fr/details/tma0505s/convertisseurs-dc-dc/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
U6 | 1 | DS18B20+ |  | https://www.tme.eu/fr/details/ds18b20+/transmetteurs-de-temp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
 | 1 | Module Atlas EZO pH |  | https://www.digikey.fr/fr/products/detail/atlas-scientific/E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
 | 1 | Module Atlas EZO ORP |  | https://www.digikey.fr/fr/products/detail/atlas-scientific/E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
 | 1 | Sonde pH connecteur BNC
 | 1 | Sonde ORP connecteur BNC
 | 1 | Module RTC DS3231 |  | https://fr.aliexpress.com/item/1005010435328928.html?spm=a2g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
 | 0 | module ADC ADS1115
 | 1 | Finder 22.32.0.012.4340 | Si contrôle filtration : Contacteur rail DIN 12V / 220V 25A
 | 1 | Finder 22.32.0.012.4340 | Si contrôle éclairage : Contacteur rail DIN 12V / 220V 25A
 | 2 | Pompe PŽristaltique 12V 90ml/min 12V-S10B avec tuyau en BPT PharMed (plus simpl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 |  | https://fr.aliexpress.com/item/1005008568962671.html?spm=a2g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
 | 1 | Si tuyau pompe pas en Pharmed : tuyau Pharmed ˆ la coupe |  | https://fr.aliexpress.com/item/1005005939700189.html?spm=a2g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
 | 2 | Raccord ou clapet anti-retour en PVDF vers tuyau injection 4x6. Taille 1/8'' |  | https://fr.aliexpress.com/item/32721015040.html?spm=a2g0o.or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
 | 2 | Tuyau 4x6mm en PE pour raccorder tuyau pompe au bidon de produit |  | https://eau2.fr/tube-pe-chlore-et-ph/597-49-tube-pe-4x6mm-ch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
 | 1 | Alimentation Rail DIN : Mean Well HDR-30-12 2A |  | https://www.amazon.fr/dp/B071KXJPYB?ref=ppx_yo2ov_dt_b_fed_a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
 | 2 | Clapet d'injection raccord 1/2'' Chlore ou pH |  | https://eau2.fr/analyseur-pieces-detachees-astralpool/404-cl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
 | 1 | Collecteur piscine porte sonde diamtre 50 |  | https://jardiboutique.com/fr/regulateur-ph-rx/15015-collecte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
 | 2 | Filtre aspiration pompe doseuse |  | https://eau2.fr/aspiration-du-chlore-liquide-et-ph-moins/733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

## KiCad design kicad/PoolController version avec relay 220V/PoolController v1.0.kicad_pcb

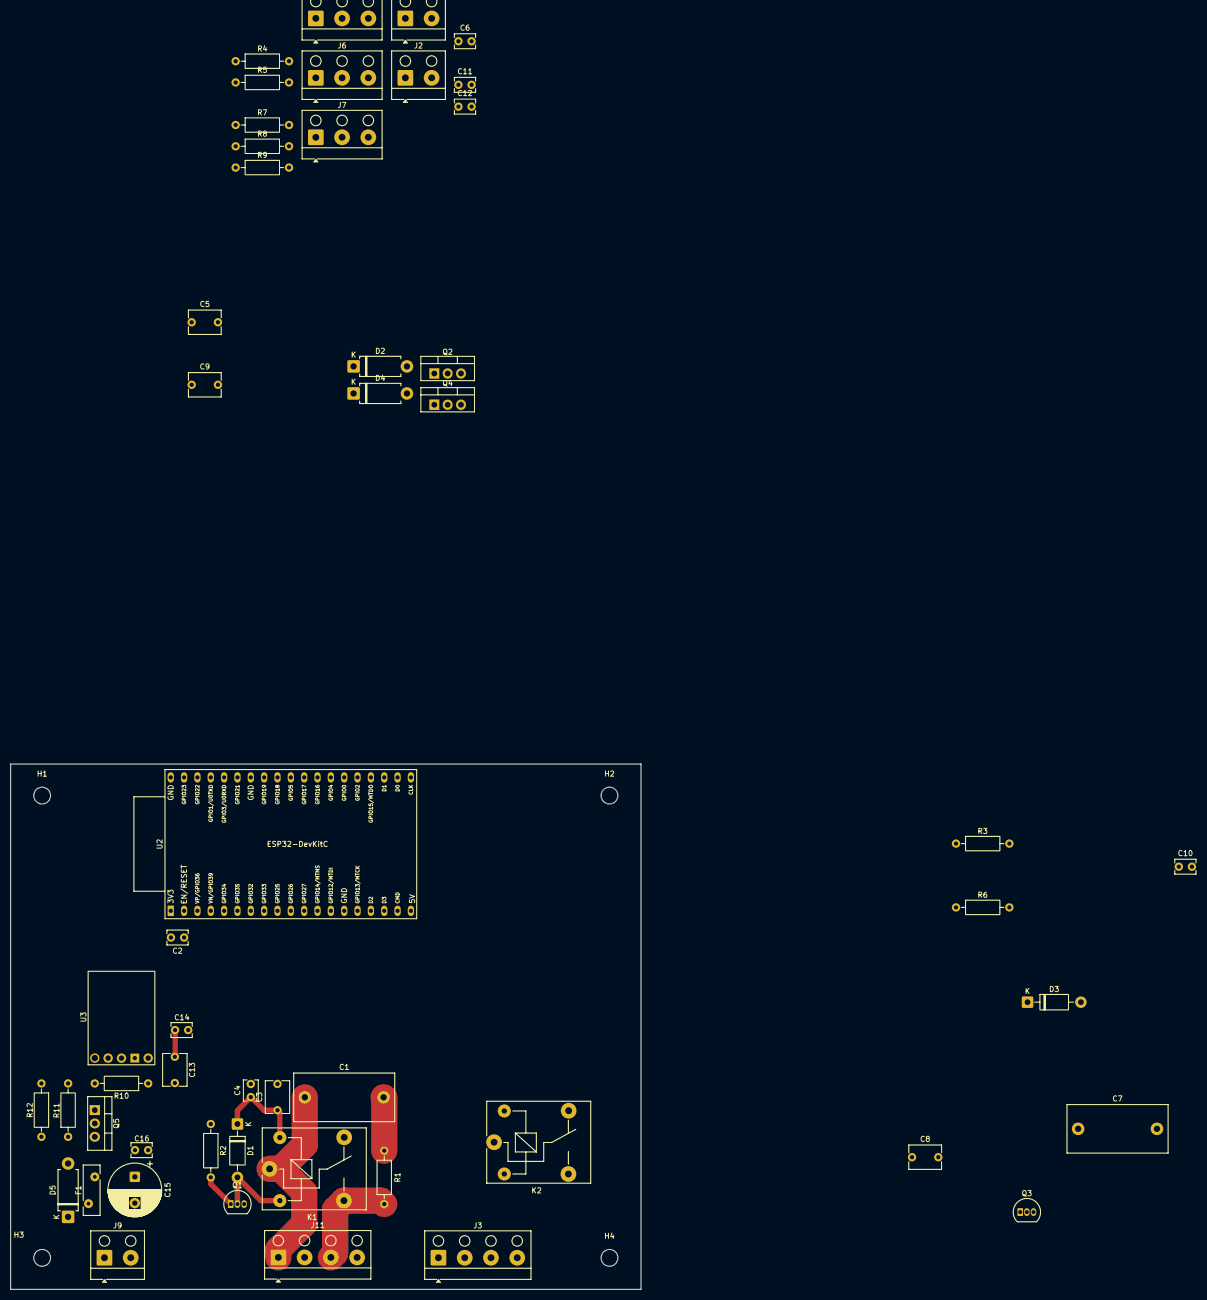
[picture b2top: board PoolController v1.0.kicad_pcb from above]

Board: 2 copper layers, 120.0 x 100.0 mm, 55 parts (0 on the bottom side), 29 nets.

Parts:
C1, C7: PME271MB6100MR30; C_Rect_L19.0mm_W9.0mm_P15.00mm_MKS4
C2, C4, C6, C10, C11, C12, C14, C16: 100nF; C_Disc_D3.8mm_W2.6mm_P2.50mm
C3, C5, C8, C9, C13: 10 µF; C_Disc_D6.0mm_W4.4mm_P5.00mm
C15: 470µF; CP_Radial_D10.0mm_P5.00mm
D1, D3: 1N4007; D_DO-41_SOD81_P10.16mm_Horizontal
D2, D4: 1N5819; D_DO-15_P10.16mm_Horizontal
D5: P6KE13A; D_DO-15_P10.16mm_Horizontal
F1: FX200-16; Fuse_Bourns_MF-RHT200
H1, H2, H3, H4: MountingHole; MountingHole_3.2mm_M3
J1, J2: Pompe Péristaltique; Altech_AK100_1x02_P5.00mm
J3, J11: Eclairage; Altech_AK100_1x04_P5.00mm
J4: Sonde température DS18B20; Altech_AK100_1x03_P5.00mm
J6, J7: Conn_01x03; Altech_AK100_1x03_P5.00mm
J9: Alimentation 12V (2A min); Altech_AK100_1x02_P5.00mm
K1, K2: SANYOU_SRD_Form_C; Relay_SPDT_SANYOU_SRD_Series_Form_C
Q1, Q3: PN2222A; TO-92_Inline
Q2, Q4: IRLZ44N; TO-220-3_Vertical
Q5: IRF4905; TO-220-3_Vertical
R1, R3, R4, R7: 100Ω; R_Axial_DIN0207_L6.3mm_D2.5mm_P10.16mm_Horizontal
R2, R6: 330Ω; R_Axial_DIN0207_L6.3mm_D2.5mm_P10.16mm_Horizontal
R5, R8, R10, R12: 10KΩ; R_Axial_DIN0207_L6.3mm_D2.5mm_P10.16mm_Horizontal
R9: 4.7KΩ; R_Axial_DIN0207_L6.3mm_D2.5mm_P10.16mm_Horizontal
R11: 10Ω; R_Axial_DIN0207_L6.3mm_D2.5mm_P10.16mm_Horizontal
U2: ESP32-DevKitC
U3: D24V10F3; Pololu_D24V10F3

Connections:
+3.3V: C2.2, C3.1, C4.1, C8.1, C10.1, C12.2, C13.1, C14.1, D1.1 (K), D3.1 (K), J4.2, J6.1, J7.1, K1.5, K2.5, R9.1, U2.1 (3V3), U3.5 (VOUT)
+12V: C5.1, C6.1, C9.1, C11.1, D2.1 (K), D4.1 (K), F1.1, J1.1, J2.1, J9.1, Q5.2 (D), R10.1, U3.3 (VIN)
/230V_IN_ECLAIRAGE: C1.1, J11.1, K1.1
/230V_IN_FILTRATION: C7.1, J3.1, K2.1
/230V_OUT_ECLAIRAGE: J11.3, K1.3, R1.1
/230V_OUT_FILTRATION: J3.3, K2.3, R3.1
/DATA_DS18B20: J4.3, R9.2, U2.5 (VDET_1/GPIO34/ADC1_CH6)
/DATA_ORP: J7.3, U2.8 (32K_XN/GPIO33/ADC1_CH5)
/DATA_PH: J6.3, U2.7 (32K_XP/GPIO32/ADC1_CH4)
/POMPE_1: R4.2, U2.15 (MTCK/GPIO13/ADC2_CH4)
/POMPE_2: R7.2, U2.12 (MTMS/GPIO14/ADC2_CH6)
/RELAIS_1: R2.1, U2.10 (DAC_2/ADC2_CH9/GPIO26)
/RELAIS_2: R6.1, U2.11 (ADC2_CH7/GPIO27)
GND: C2.1, C3.2, C4.2, C5.2, C6.2, C8.2, C9.2, C10.2, C11.2, C12.1, C13.2, C14.2, C15.2, C16.2, D5.1 (A1), J4.1, J6.2, J7.2, J9.2, Q1.3 (C), Q2.3 (S), Q3.3 (C), Q4.3 (S), R5.2, R8.2, R12.2, U2.14 (GND), U2.32 (GND), U2.38 (GND), U3.4 (GND)
unnamed: C1.2, R1.2
unnamed: C7.2, R3.2
unnamed: D1.2 (A), K1.2, Q1.2 (B)
unnamed: D2.2 (A), J1.2, Q2.2 (D)
unnamed: D3.2 (A), K2.2, Q3.2 (B)
unnamed: D4.2 (A), J2.2, Q4.2 (D)
unnamed: C15.1, C16.1, D5.2 (A2), F1.2, Q5.3 (S), R11.1
unnamed: J3.2, J3.4
unnamed: J11.2, J11.4
unnamed: Q1.1 (E), R2.2
unnamed: Q2.1 (G), R4.1, R5.1
unnamed: Q3.1 (E), R6.2
unnamed: Q4.1 (G), R7.1, R8.1
unnamed: Q5.1 (G), R11.2, R12.1
unnamed: R10.2, U3.2 (SHDN)

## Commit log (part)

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2026-04-07 chore(deps-dev): bump picomatch
    Bumps the npm_and_yarn group with 1 update in the / directory: [picomatch](https://github.com/micromatch/picomatch).
    Updates `picomatch` from 2.3.1 to 2.3.2
    - [Release notes](https://github.com/micromatch/picomatch/releases)
    - [Changelog](https://github.com/micromatch/picomatch/blob/master/CHANGELOG.md)
    - [Commits](https://github.com/micromatch/picomatch/compare/2.3.1...2.3.2)
    ---
2026-05-08 feat(ph/orp): migration Atlas EZO + outils debug oscillation (feature-021)
    Migration complète de la chaîne pH/ORP : ADS1115 + DFRobot_PH → modules
    Atlas Scientific EZO Embedded I²C (pH 0x63, ORP 0x62) sur PCB v2. Inclut
    hotfix oscillation cyclique identifiée pendant debug terrain et outils
    de diagnostic intégrés à l'UI.
    == Firmware (Atlas EZO) ==
    - src/atlas_ezo.h/cpp (NOUVEAU) : mini-classe AtlasEzoSensor. Mutex I²C
2026-05-08 chore(partitions): app à 1.5 MB / spiffs 832 KB (layout v2, ADR-0015)
    L'implémentation de feature-024 (pente sonde pH) a fait franchir la
    limite de la partition app1 (1408 KB) au firmware (1446 KB image .bin).
    Bootloader détectait CRC invalide → SW_RESET en boucle au démarrage.
    == Nouveau layout (4 MB flash) ==
    - app0 : 0x10000 → 0x180000 (1408 KB → 1536 KB, +128 KB)
    - app1 : 0x190000 → 0x180000 (1408 KB → 1536 KB, +128 KB)
2026-05-08 feat(ph): pente sonde pH Atlas EZO + chip santé sur page /ph (feature-024)
    Expose la santé de la sonde pH via la commande Atlas EZO Slope,? (pente
    acide %, pente base %, décalage zéro mV). Permet à l'utilisateur de
    diagnostiquer l'usure d'une sonde avant que la régulation devienne
    erratique. Feature strictement diagnostique : aucun impact sur canDose(),
    le PID ou le dosage.
    == Firmware ==
2026-05-08 fix(history): détection corruption LittleFS + reformatage automatique au boot
    LittleFS peut monter un filesystem corrompu sans erreur puis crasher
    en IntegerDivideByZero à la 1ère écriture (bug interne LittleFS connu,
    documenté dans le code ligne 70). Symptôme observé sur ESP32 PCB v1
    après une longue période d'inactivité — boot loop sans message
    d'erreur après "Partition historique dédiée montée".
    Le mécanisme préventif existant ne détectait que les changements de
2026-05-10 fix(sensors): underflow uint32 dans la garde 24h Slope query (feature-024)
    Sans rafraîchir `now` après _processEzoQueue() (qui peut bloquer ~900ms
    sur la commande I²C `Slope,?`), la condition de re-query 24h dans
    SensorManager::update() sous-flow en uint32 dès la 1ʳᵉ query Slope
    réussie → ré-enqueue à chaque cycle update() → spam de query Slope
    toutes les ~secondes (1 log/s observé en condition réelle).
    == Séquence du bug ==
2026-05-10 feat(debug): outil diagnostic commandes EZO + endpoint factory reset
    Ajoute 2 endpoints HTTP et une carte UI pour interroger les modules Atlas
    EZO en envoyant n'importe quelle commande arbitraire et observer la réponse
    brute. Outil indispensable pour diagnostiquer les modules qui ne répondent
    pas comme attendu (cf. analyse séquence pH/ORP feature-021).
    == Endpoints ==
    - POST /debug/ezo_command (body JSON {addr, cmd, delay_ms})
2026-05-10 fix(sensors): EZO ORP utilise R au lieu de RT,<t> (pas de payload sur ORP)
    Le firmware envoyait RT,<temp> indistinctement aux 2 modules Atlas. Sur
    l'EZO pH, RT,<t> compense la T° (Nernst) ET retourne la valeur pH compensée.
    Sur l'EZO ORP, RT,<t> est ACCEPTÉ (status=1 success) mais ne retourne PAS
    de payload (resp vide) car l'ORP est potentiométrique direct sans
    compensation T° à effectuer.
    Le firmware attendait un payload qui ne venait jamais → readSingle()
2026-05-10 fix(security): rate limit 30 → 120 req/min pour usage UI normal
    L'ancienne limite de 30 req/min était trop basse et déclenchait des
    warnings "Rate limit dépassé" en navigation normale dans l'UI :
    - Page /params ouverte : ~6-12 polls /get-config par minute
    - Page /data refresh : ~2 par minute
    - /coredump/info, autres polls : ~2-4 par minute
    - Clics utilisateur sur boutons (debug EZO notamment) : variable
2026-05-10 docs(v2.1.1): documenter les 4 fixes + outil diagnostic EZO
    Documente les 5 commits récents sur pcb-v2 :
    - 3c8b657 fix(history) détection corruption LittleFS
    - 933f17c fix(sensors) underflow uint32 slope query
    - 20e4a9b feat(debug) outil diagnostic EZO (commandes manuelles)
    - c0f2962 fix(sensors) EZO ORP utilise R au lieu de RT
    - 6c79cfc fix(security) rate limit 30 → 120 req/min
2026-05-10 fix(safety): arrêter l'injection manuelle si filtration KO + UI feedback (v2.1.2)
    Bug observé en production PCB v1 : injection manuelle volumée pH lancée
    pendant filtration active continue après l'arrêt programmé de la filtration
    → surdosage local d'acide dans la zone du retour d'eau (eau qui ne circule
    plus = corrosion + risque sanitaire).
    Validation pool-chemistry GO sous conditions, toutes appliquées.
    == Backend (src/) ==
2026-06-23 Update PCB image in README.md
    PCB update

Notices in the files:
README.md:
📄 Licence:
MIT License - Voir fichier LICENSE
